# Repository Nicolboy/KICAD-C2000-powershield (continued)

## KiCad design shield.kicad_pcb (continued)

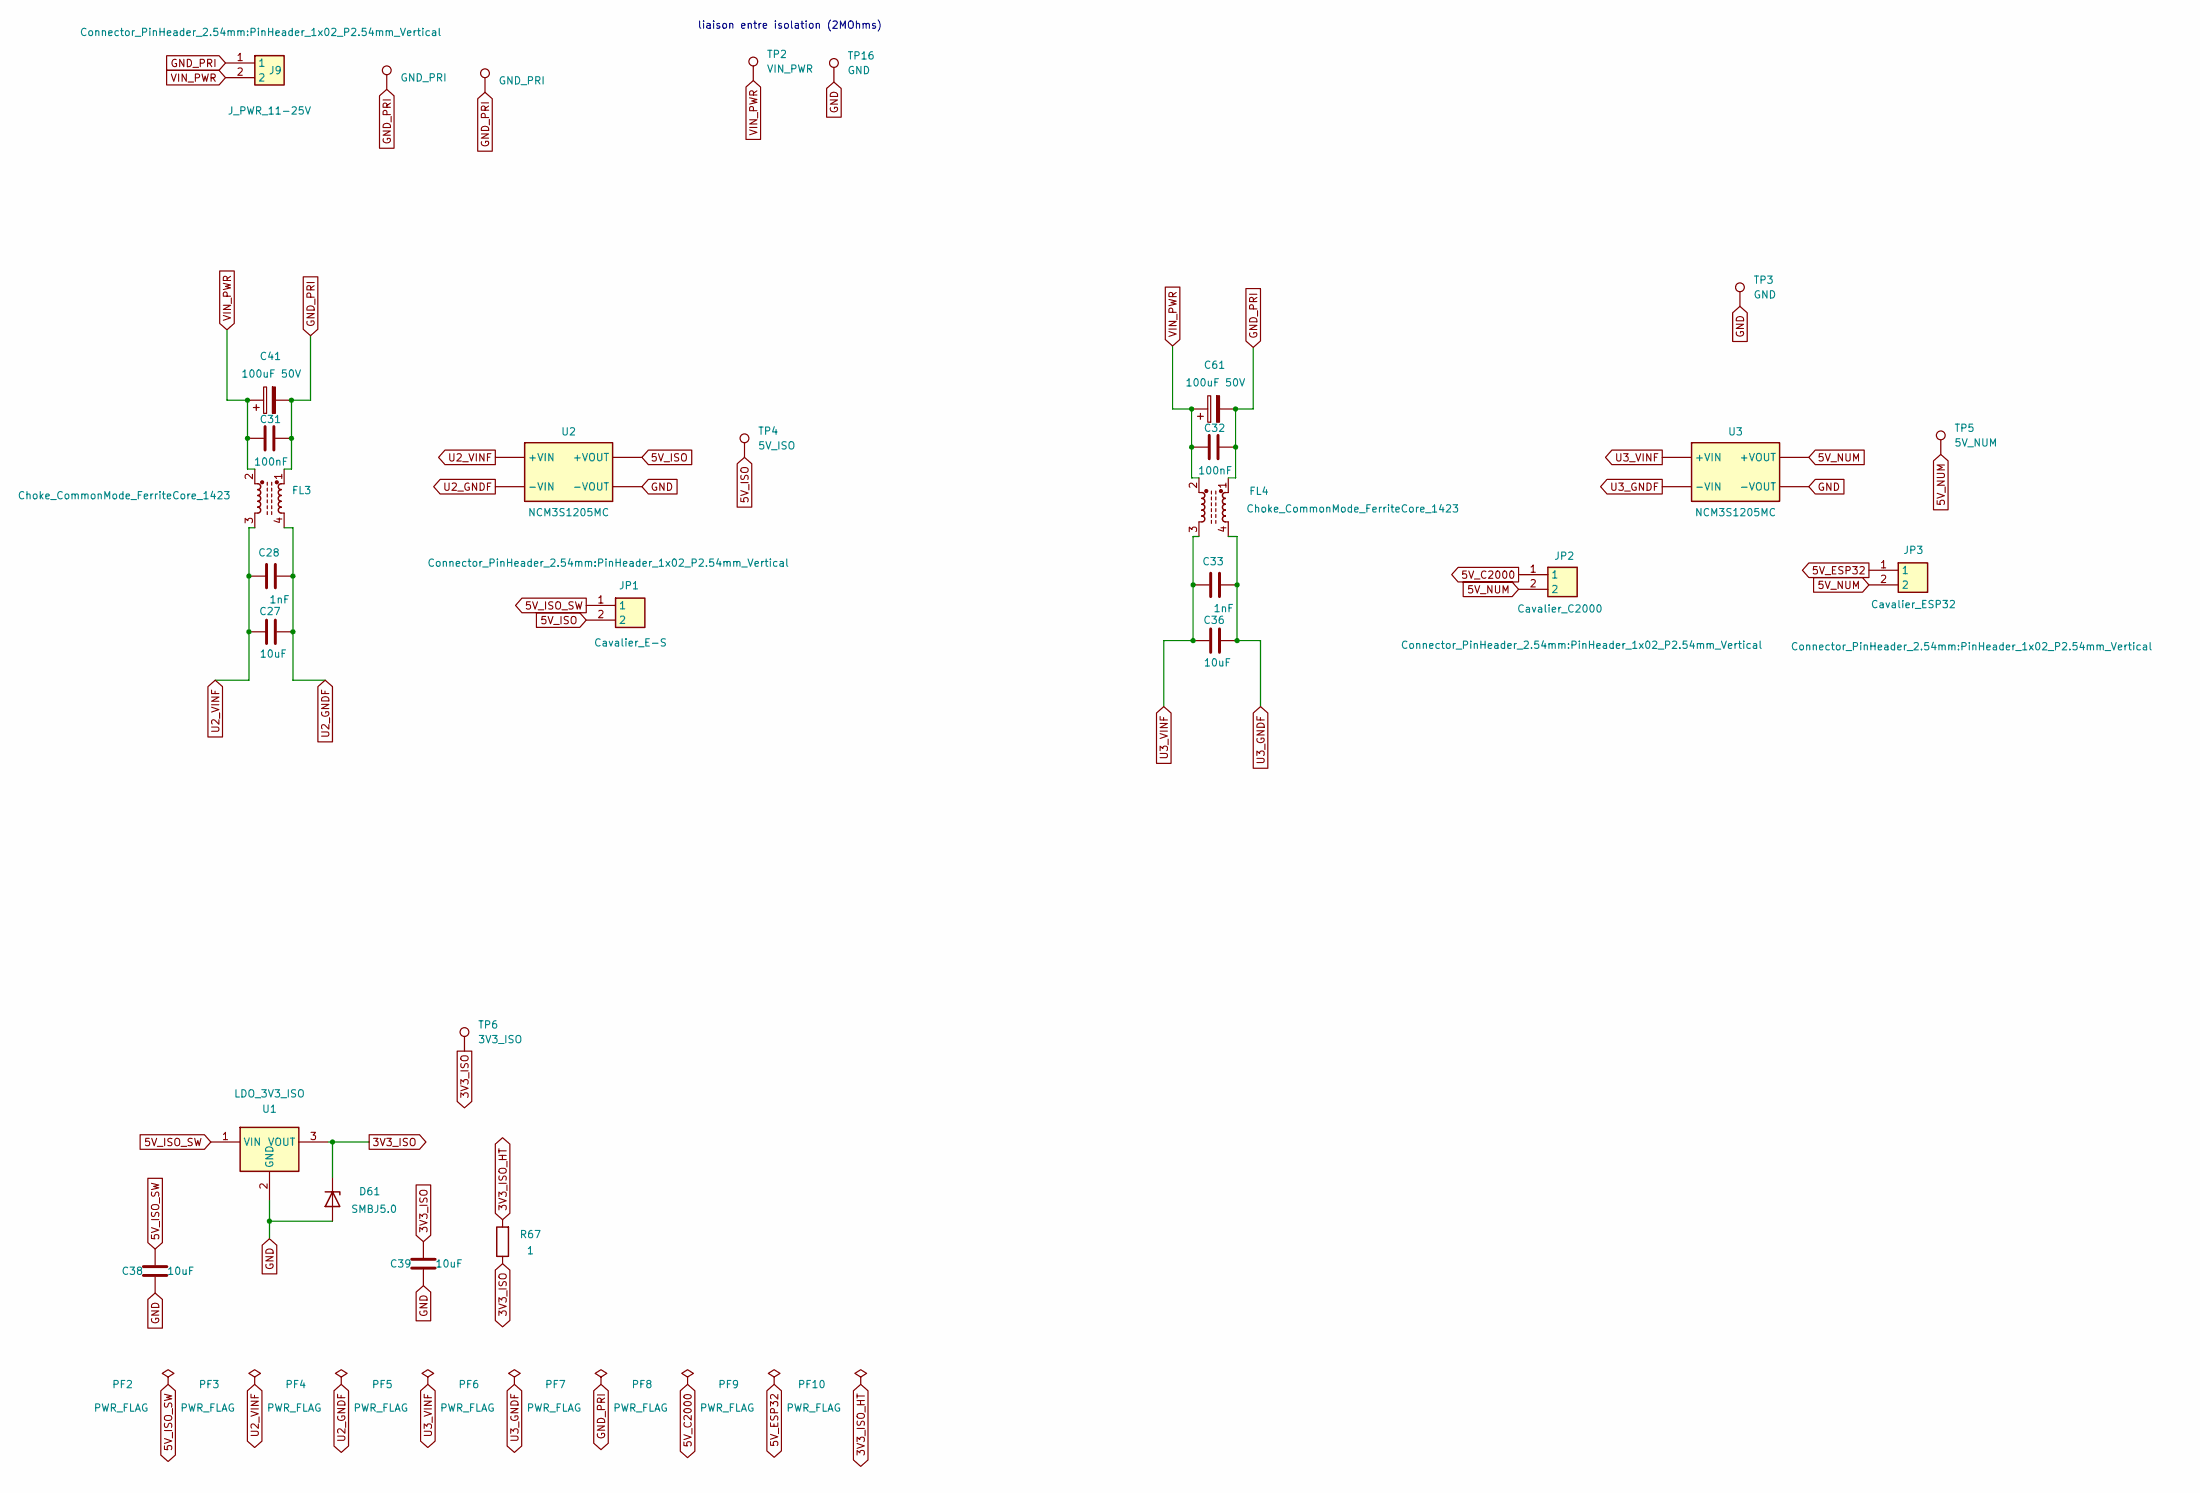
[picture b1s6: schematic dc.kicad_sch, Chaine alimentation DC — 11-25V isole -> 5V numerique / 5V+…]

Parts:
C27, C36, C38, C39: 10uF; C_0805_2012Metric
C28, C33: 1nF; C_0805_2012Metric
C31, C32: 100nF; C_0805_2012Metric
C41, C61: 100uF 50V; CP_Elec_8x10.5
D61: SMBJ5.0; D_SMB
FL3, FL4: Choke_CommonMode_FerriteCore_1423; Filter_Bourns_SRF0905_6.0x9.2mm_My
J9: J_PWR_11-25V; PinHeader_1x02_P2.54mm_Vertical
JP1: Cavalier_E-S; PinHeader_1x02_P2.54mm_Vertical
JP2: Cavalier_C2000; PinHeader_1x02_P2.54mm_Vertical
JP3: Cavalier_ESP32; PinHeader_1x02_P2.54mm_Vertical
PF2, PF3, PF4, PF5, PF6, PF7, PF8, PF9, PF10: PWR_FLAG
R67: 1; R_0805_2012Metric
TP1, TP15: GND_PRI; TestPoint_Pad_D2.5mm
TP2: VIN_PWR; TestPoint_Pad_D2.5mm
TP3, TP16: GND; TestPoint_Pad_D2.5mm
TP4: 5V_ISO; TestPoint_Pad_D2.5mm
TP5: 5V_NUM; TestPoint_Pad_D2.5mm
TP6: 3V3_ISO; TestPoint_Pad_D2.5mm
U1: LDO_3V3_ISO; SOT-23
U2, U3: NCM3S1205MC

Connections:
3V3_ISO: C39.1, D61.1 (K), R67.1, TP6.1 (1_1), U1.3 (VOUT)
3V3_ISO_HT: PF10.1, R67.2; also elsewhere on the board
5V_C2000: JP2.1, PF8.1; also elsewhere on the board
5V_ESP32: JP3.1, PF9.1; also elsewhere on the board
5V_ISO: JP1.2, TP4.1 (1_1), U2.3 (+VOUT)
5V_ISO_SW: C38.1, JP1.1, PF2.1, U1.1 (VIN); also elsewhere on the board
5V_NUM: JP2.2, JP3.2, TP5.1 (1_1), U3.3 (+VOUT)
GND: C38.2, C39.2, D61.2 (A), TP3.1 (1_1), TP16.1 (1_1), U1.2 (GND), U2.4 (-VOUT), U3.4 (-VOUT); also elsewhere on the board
GND_PRI: C31.2, C32.2, C41.2, C61.2, FL3.1, FL4.1, J9.1, PF7.1, TP1.1 (1_1), TP15.1 (1_1); also elsewhere on the board
U2_GNDF: C27.1, C28.2, FL3.4, PF4.1, U2.1 (-VIN)
U2_VINF: C27.2, C28.1, FL3.3, PF3.1, U2.2 (+VIN)
U3_GNDF: C33.2, C36.1, FL4.4, PF6.1, U3.1 (-VIN)
U3_VINF: C33.1, C36.2, FL4.3, PF5.1, U3.2 (+VIN)
VIN_PWR: C31.1, C32.1, C41.1, C61.1, FL3.2, FL4.2, J9.2, TP2.1 (1_1); also elsewhere on the board

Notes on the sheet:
liaison entre isolation (2MOhms)

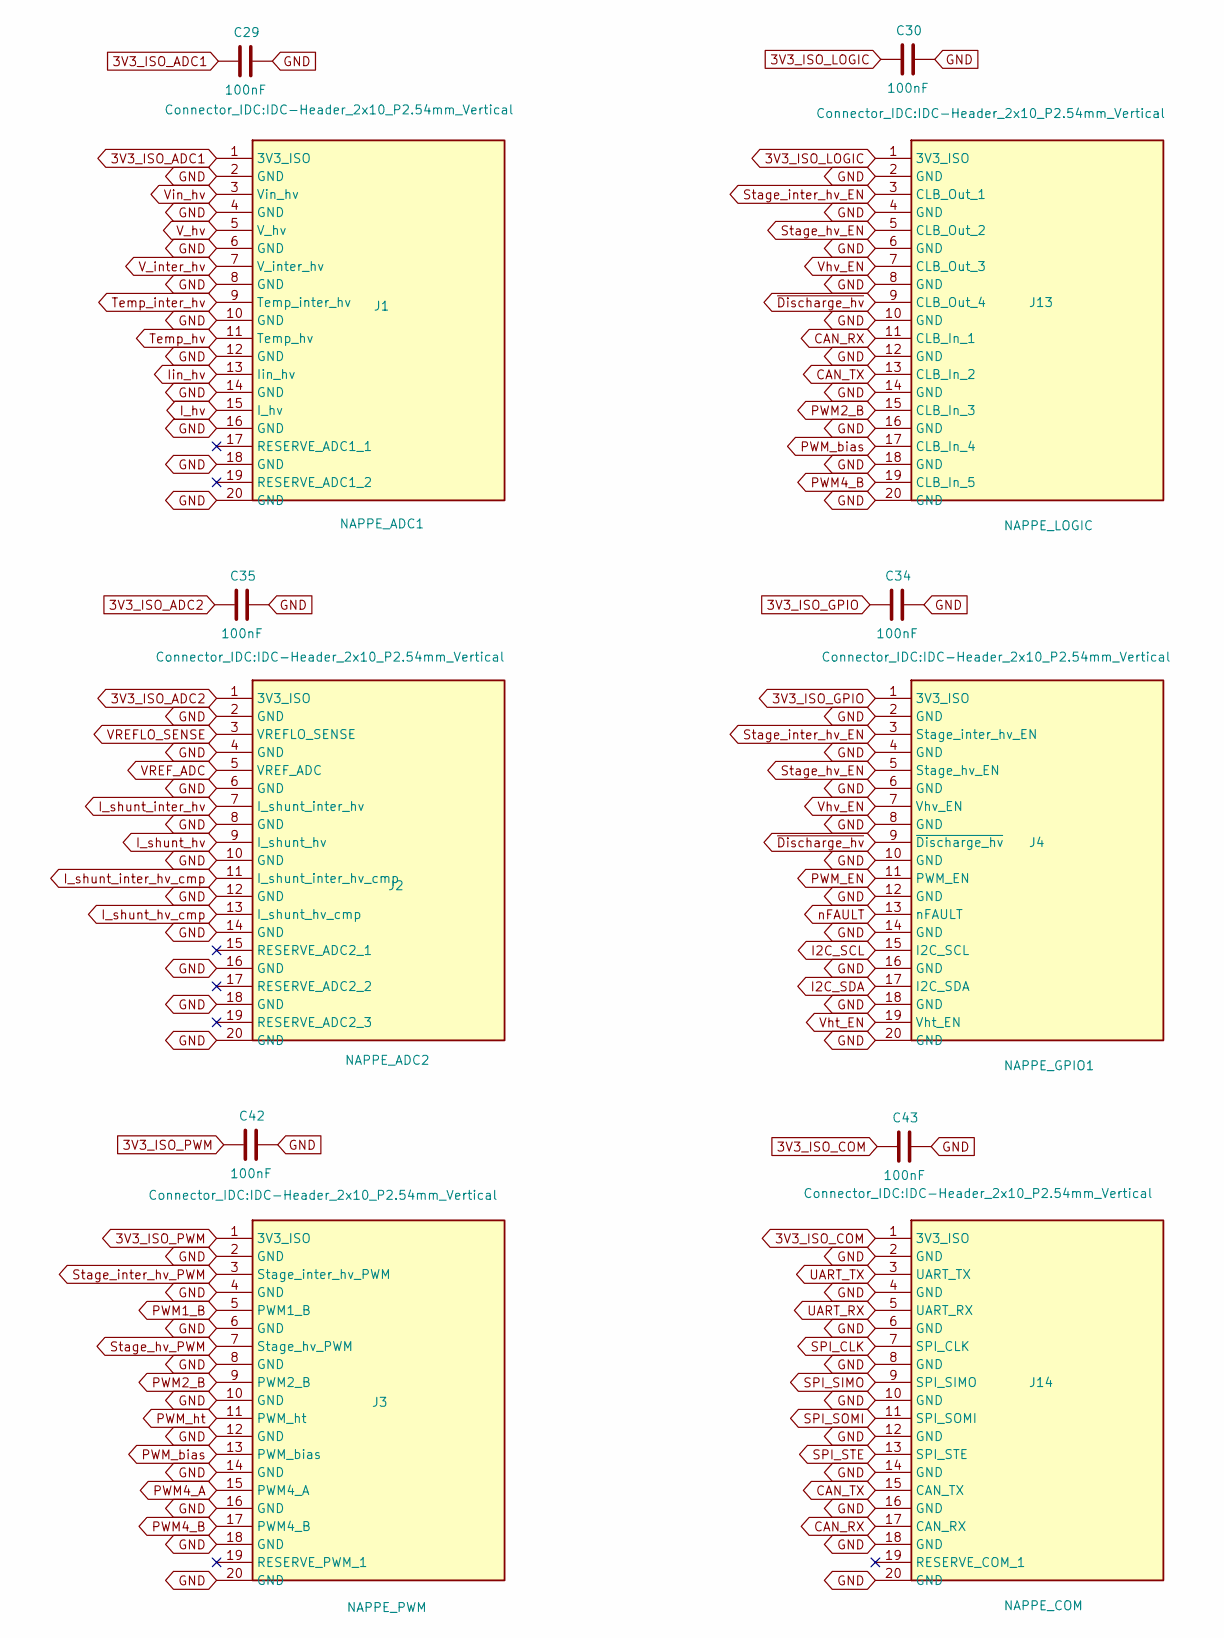
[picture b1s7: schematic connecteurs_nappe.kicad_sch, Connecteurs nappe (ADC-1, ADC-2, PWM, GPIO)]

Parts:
C29, C30, C34, C35, C42, C43: 100nF; C_0805_2012Metric
J1: NAPPE_ADC1; IDC-Header_2x10_P2.54mm_Vertical
J2: NAPPE_ADC2; IDC-Header_2x10_P2.54mm_Vertical
J3: NAPPE_PWM; IDC-Header_2x10_P2.54mm_Vertical
J4: NAPPE_GPIO1; IDC-Header_2x10_P2.54mm_Vertical
J13: NAPPE_LOGIC; IDC-Header_2x10_P2.54mm_Vertical
J14: NAPPE_COM; IDC-Header_2x10_P2.54mm_Vertical

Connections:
3V3_ISO_ADC1: C29.1, J1.1 (3V3_ISO); also elsewhere on the board
3V3_ISO_ADC2: C35.1, J2.1 (3V3_ISO); also elsewhere on the board
3V3_ISO_COM: C43.1, J14.1 (3V3_ISO); also elsewhere on the board
3V3_ISO_GPIO: C34.1, J4.1 (3V3_ISO); also elsewhere on the board
3V3_ISO_LOGIC: C30.1, J13.1 (3V3_ISO); also elsewhere on the board
3V3_ISO_PWM: C42.1, J3.1 (3V3_ISO); also elsewhere on the board
CAN_RX: J13.11 (CLB_In_1), J14.17 (CAN_RX); also elsewhere on the board
CAN_TX: J13.13 (CLB_In_2), J14.15 (CAN_TX); also elsewhere on the board
GND: C29.2, C30.2, C34.2, C35.2, C42.2, C43.2, J1.2 (GND), J1.4 (GND), J1.6 (GND), J1.8 (GND), J1.10 (GND), J1.12 (GND), J1.14 (GND), J1.16 (GND), J1.18 (GND), J1.20 (GND), J2.2 (GND), J2.4 (GND), J2.6 (GND), J2.8 (GND), J2.10 (GND), J2.12 (GND), J2.14 (GND), J2.16 (GND), J2.18 (GND), J2.20 (GND), J3.2 (GND), J3.4 (GND), J3.6 (GND), J3.8 (GND), J3.10 (GND), J3.12 (GND), J3.14 (GND), J3.16 (GND), J3.18 (GND), J3.20 (GND), J4.2 (GND), J4.4 (GND), J4.6 (GND), J4.8 (GND), J4.10 (GND), J4.12 (GND), J4.14 (GND), J4.16 (GND), J4.18 (GND), J4.20 (GND), J13.2 (GND), J13.4 (GND), J13.6 (GND), J13.8 (GND), J13.10 (GND), J13.12 (GND), J13.14 (GND), J13.16 (GND), J13.18 (GND), J13.20 (GND), J14.2 (GND), J14.4 (GND), J14.6 (GND), J14.8 (GND), J14.10 (GND), J14.12 (GND), J14.14 (GND), J14.16 (GND), J14.18 (GND), J14.20 (GND); also elsewhere on the board
I2C_SCL: J4.15 (I2C_SCL); also elsewhere on the board
I2C_SDA: J4.17 (I2C_SDA); also elsewhere on the board
I_hv: J1.15 (I_hv); also elsewhere on the board
I_shunt_hv: J2.9 (I_shunt_hv); also elsewhere on the board
I_shunt_hv_cmp: J2.13 (I_shunt_hv_cmp); also elsewhere on the board
I_shunt_inter_hv: J2.7 (I_shunt_inter_hv); also elsewhere on the board
I_shunt_inter_hv_cmp: J2.11 (I_shunt_inter_hv_cmp); also elsewhere on the board
Iin_hv: J1.13 (Iin_hv); also elsewhere on the board
PWM1_B: J3.5 (PWM1_B); also elsewhere on the board
PWM2_B: J3.9 (PWM2_B), J13.15 (CLB_In_3); also elsewhere on the board
PWM4_A: J3.15 (PWM4_A); also elsewhere on the board
PWM4_B: J3.17 (PWM4_B), J13.19 (CLB_In_5); also elsewhere on the board
PWM_EN: J4.11 (PWM_EN); also elsewhere on the board
PWM_bias: J3.13 (PWM_bias), J13.17 (CLB_In_4); also elsewhere on the board
PWM_ht: J3.11 (PWM_ht); also elsewhere on the board
SPI_CLK: J14.7 (SPI_CLK); also elsewhere on the board
SPI_SIMO: J14.9 (SPI_SIMO); also elsewhere on the board
SPI_SOMI: J14.11 (SPI_SOMI); also elsewhere on the board
SPI_STE: J14.13 (SPI_STE); also elsewhere on the board
Stage_hv_EN: J4.5 (Stage_hv_EN), J13.5 (CLB_Out_2); also elsewhere on the board
Stage_hv_PWM: J3.7 (Stage_hv_PWM); also elsewhere on the board
Stage_inter_hv_EN: J4.3 (Stage_inter_hv_EN), J13.3 (CLB_Out_1); also elsewhere on the board
Stage_inter_hv_PWM: J3.3 (Stage_inter_hv_PWM); also elsewhere on the board
Temp_hv: J1.11 (Temp_hv); also elsewhere on the board
Temp_inter_hv: J1.9 (Temp_inter_hv); also elsewhere on the board
UART_RX: J14.5 (UART_RX); also elsewhere on the board
UART_TX: J14.3 (UART_TX); also elsewhere on the board
VREFLO_SENSE: J2.3 (VREFLO_SENSE); also elsewhere on the board
VREF_ADC: J2.5 (VREF_ADC); also elsewhere on the board
V_hv: J1.5 (V_hv); also elsewhere on the board
V_inter_hv: J1.7 (V_inter_hv); also elsewhere on the board
Vht_EN: J4.19 (Vht_EN); also elsewhere on the board
Vhv_EN: J4.7 (Vhv_EN), J13.7 (CLB_Out_3); also elsewhere on the board
Vin_hv: J1.3 (Vin_hv); also elsewhere on the board
nFAULT: J4.13 (nFAULT); also elsewhere on the board
~Discharge_hv: J4.9 (~Discharge_hv), J13.9 (CLB_Out_4); also elsewhere on the board

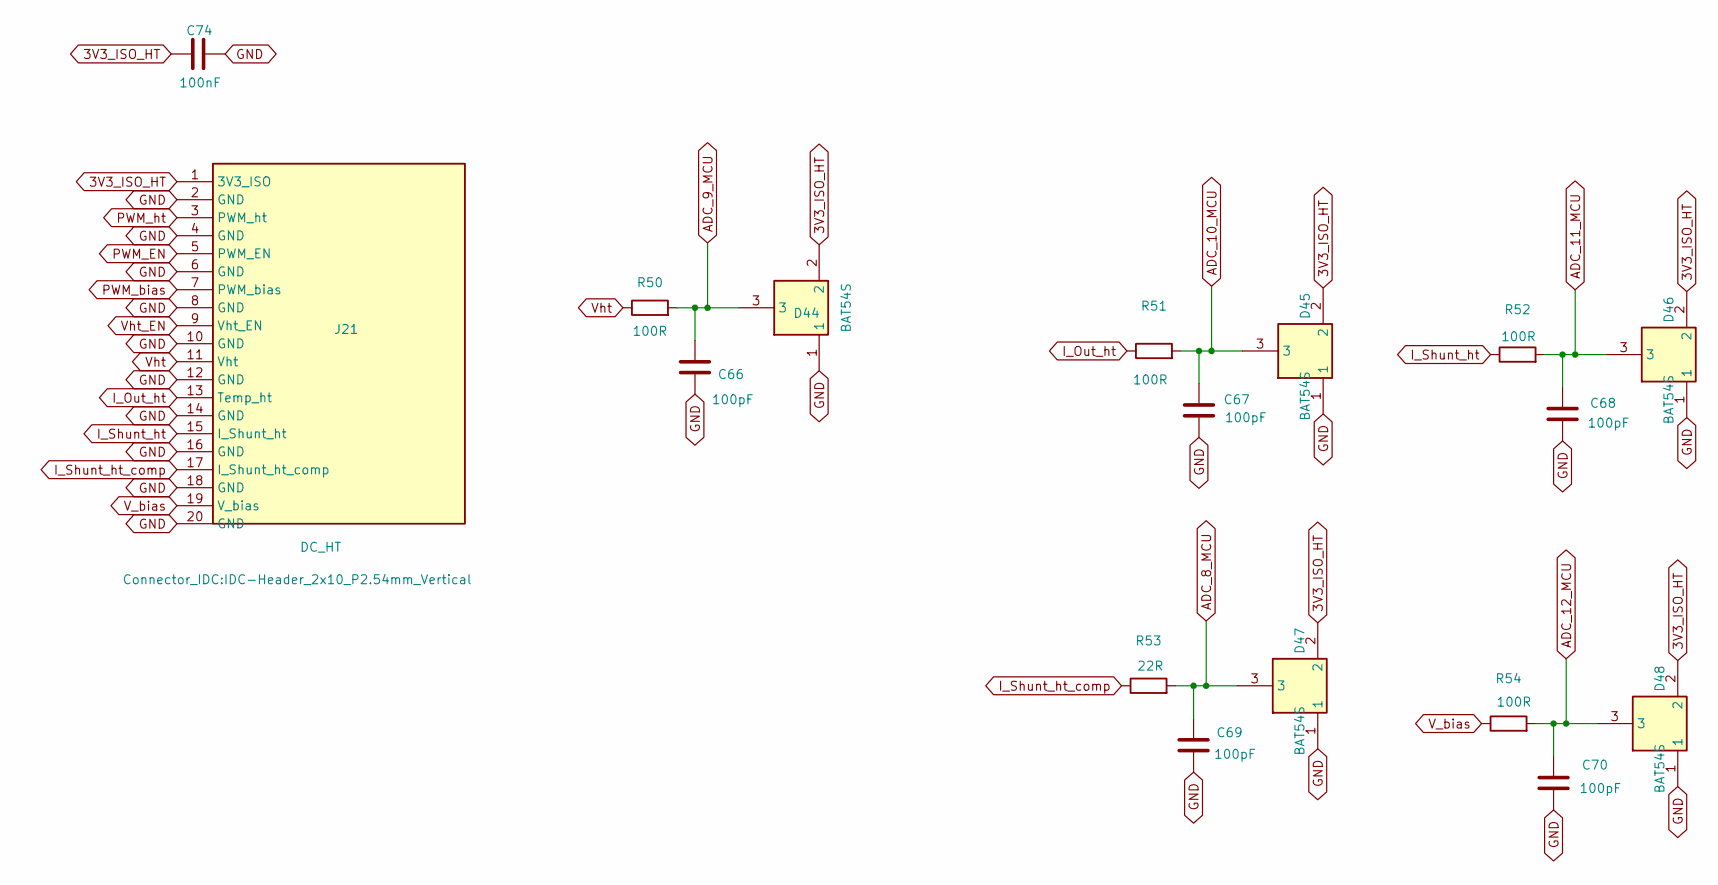
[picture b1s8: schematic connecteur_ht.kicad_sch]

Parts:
C66, C67, C68, C69, C70: 100pF; C_0805_2012Metric
C74: 100nF; C_0805_2012Metric
D44, D45, D46, D47, D48: BAT54S; SOT-23
J21: DC_HT; IDC-Header_2x10_P2.54mm_Vertical
R50, R51, R52, R54: 100R; R_0805_2012Metric
R53: 22R; R_0805_2012Metric

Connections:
3V3_ISO_HT: C74.1, D44.2, D45.2, D46.2, D47.2, D48.2, J21.1 (3V3_ISO); also elsewhere on the board
ADC_8_MCU: C69.1, D47.3, R53.2; also elsewhere on the board
ADC_9_MCU: C66.1, D44.3, R50.2; also elsewhere on the board
ADC_10_MCU: C67.1, D45.3, R51.2; also elsewhere on the board
ADC_11_MCU: C68.1, D46.3, R52.2; also elsewhere on the board
ADC_12_MCU: C70.1, D48.3, R54.2; also elsewhere on the board
GND: C66.2, C67.2, C68.2, C69.2, C70.2, C74.2, D44.1, D45.1, D46.1, D47.1, D48.1, J21.2 (GND), J21.4 (GND), J21.6 (GND), J21.8 (GND), J21.10 (GND), J21.12 (GND), J21.14 (GND), J21.16 (GND), J21.18 (GND), J21.20 (GND); also elsewhere on the board
I_Out_ht: J21.13 (Temp_ht), R51.1
I_Shunt_ht: J21.15 (I_Shunt_ht), R52.1
I_Shunt_ht_comp: J21.17 (I_Shunt_ht_comp), R53.1
PWM_EN: J21.5 (PWM_EN); also elsewhere on the board
PWM_bias: J21.7 (PWM_bias); also elsewhere on the board
PWM_ht: J21.3 (PWM_ht); also elsewhere on the board
V_bias: J21.19 (V_bias), R54.1
Vht: J21.11 (Vht), R50.1
Vht_EN: J21.9 (Vht_EN); also elsewhere on the board

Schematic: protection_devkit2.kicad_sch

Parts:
C11, C12, C13, C14, C15, C16, C17, C18, C19, C20: 100pF; C_0805_2012Metric
D12, D13, D14, D15, D16, D17, D18, D19, D20, D21: BAT54S; SOT-23
R11, R12, R13, R14, R15, R16, R17, R18, R19, R20: 100R; R_0805_2012Metric

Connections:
3V3_ISO_ADC2: D14.2; also elsewhere on the board
3V3_ISO_GPIO: D20.2; also elsewhere on the board
3V3_ISO_PWM: D12.2, D13.2, D15.2, D16.2, D17.2, D18.2, D19.2, D21.2; also elsewhere on the board
CMP_OUT_MCU: C19.2, D20.3, R19.2; also elsewhere on the board
GND: C11.1, C12.1, C13.1, C14.1, C15.1, C16.1, C17.1, C18.1, C19.1, C20.1, D12.1, D13.1, D14.1, D15.1, D16.1, D17.1, D18.1, D19.1, D20.1, D21.1; also elsewhere on the board
PWM1_A_MCU: C12.2, D13.3, R12.2; also elsewhere on the board
PWM1_B: R11.1; also elsewhere on the board
PWM1_B_MCU: C11.2, D12.3, R11.2; also elsewhere on the board
PWM2_A_MCU: C16.2, D17.3, R16.2; also elsewhere on the board
PWM2_B: R15.1; also elsewhere on the board
PWM2_B_MCU: C15.2, D15.3, R15.2; also elsewhere on the board
PWM3_A_MCU: C14.2, D16.3, R14.2; also elsewhere on the board
PWM3_B_MCU: C18.2, D19.3, R18.2; also elsewhere on the board
PWM4_A: R17.1; also elsewhere on the board
PWM4_A_MCU: C17.2, D18.3, R17.2; also elsewhere on the board
PWM4_B: R20.1; also elsewhere on the board
PWM4_B_MCU: C20.2, D21.3, R20.2; also elsewhere on the board
PWM_EN: R19.1; also elsewhere on the board
PWM_bias: R18.1; also elsewhere on the board
PWM_ht: R14.1; also elsewhere on the board
Stage_hv_PWM: R16.1; also elsewhere on the board
Stage_inter_hv_PWM: R12.1; also elsewhere on the board
VREFLO_SENSE: R13.1; also elsewhere on the board
VREFLO_SENSE_MCU: C13.2, D14.3, R13.2; also elsewhere on the board

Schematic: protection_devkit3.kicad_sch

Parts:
C21, C22, C23: 100pF; C_0805_2012Metric
D22, D23, D24: BAT54S; SOT-23
R21, R22, R23: 100R; R_0805_2012Metric
R68, R69: 4.7k; R_0805_2012Metric
TP7: I2C_SDA_MCU; TestPoint_Pad_D2.5mm
TP8: I2C_SCL_MCU; TestPoint_Pad_D2.5mm

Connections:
3V3_C2000: R68.1, R69.1; also elsewhere on the board
3V3_ISO_GPIO: D22.2, D23.2, D24.2; also elsewhere on the board
GND: C21.1, C22.1, C23.1, D22.1, D23.1, D24.1; also elsewhere on the board
I2C_SCL: R21.1; also elsewhere on the board
I2C_SCL_MCU: C21.2, D22.3, R21.2, R68.2, TP8.1 (1_1); also elsewhere on the board
I2C_SDA: R23.1; also elsewhere on the board
I2C_SDA_MCU: C23.2, D24.3, R23.2, R69.2, TP7.1 (1_1); also elsewhere on the board
nFAULT: R22.1; also elsewhere on the board
~FAULT_MCU: C22.2, D23.3, R22.2; also elsewhere on the board

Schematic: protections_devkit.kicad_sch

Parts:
C1, C2, C3, C4, C5, C6, C7, C8, C9: 100pF; C_0805_2012Metric
D2, D3, D4, D5, D6, D7, D8, D9, D10: BAT54S; SOT-23
R1, R2, R3, R4, R5, R6, R7, R8, R9: 100R; R_0805_2012Metric

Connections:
3V3_ISO_ADC1: D2.2, D3.2, D4.2, D5.2, D6.2, D7.2, D9.2; also elsewhere on the board
3V3_ISO_ADC2: D8.2, D10.2; also elsewhere on the board
GND: C1.1, C2.1, C3.1, C4.1, C5.1, C6.1, C7.1, C8.1, C9.1, D2.1, D3.1, D4.1, D5.1, D6.1, D7.1, D8.1, D9.1, D10.1; also elsewhere on the board
I_hv: R7.1; also elsewhere on the board
I_shunt1_MCU: C8.2, D8.3, R8.2; also elsewhere on the board
I_shunt2_MCU: C9.2, D10.3, R9.2; also elsewhere on the board
I_shunt_hv: R9.1; also elsewhere on the board
I_shunt_inter_hv: R8.1; also elsewhere on the board
Iin_MCU: C6.2, D7.3, R5.2; also elsewhere on the board
Iin_hv: R5.1; also elsewhere on the board
Iout_MCU: C7.2, D9.3, R7.2; also elsewhere on the board
Temp1_MCU: C4.2, D6.3, R4.2; also elsewhere on the board
Temp2_MCU: C5.2, D5.3, R6.2; also elsewhere on the board
Temp_hv: R6.1; also elsewhere on the board
Temp_inter_hv: R4.1; also elsewhere on the board
V1_MCU: C1.2, D3.3, R1.2; also elsewhere on the board
V_hv: R2.1; also elsewhere on the board
V_inter_hv: R1.1; also elsewhere on the board
Vin_MCU: C3.2, D4.3, R3.2; also elsewhere on the board
Vin_hv: R3.1; also elsewhere on the board
Vout_MCU: C2.2, D2.3, R2.2; also elsewhere on the board

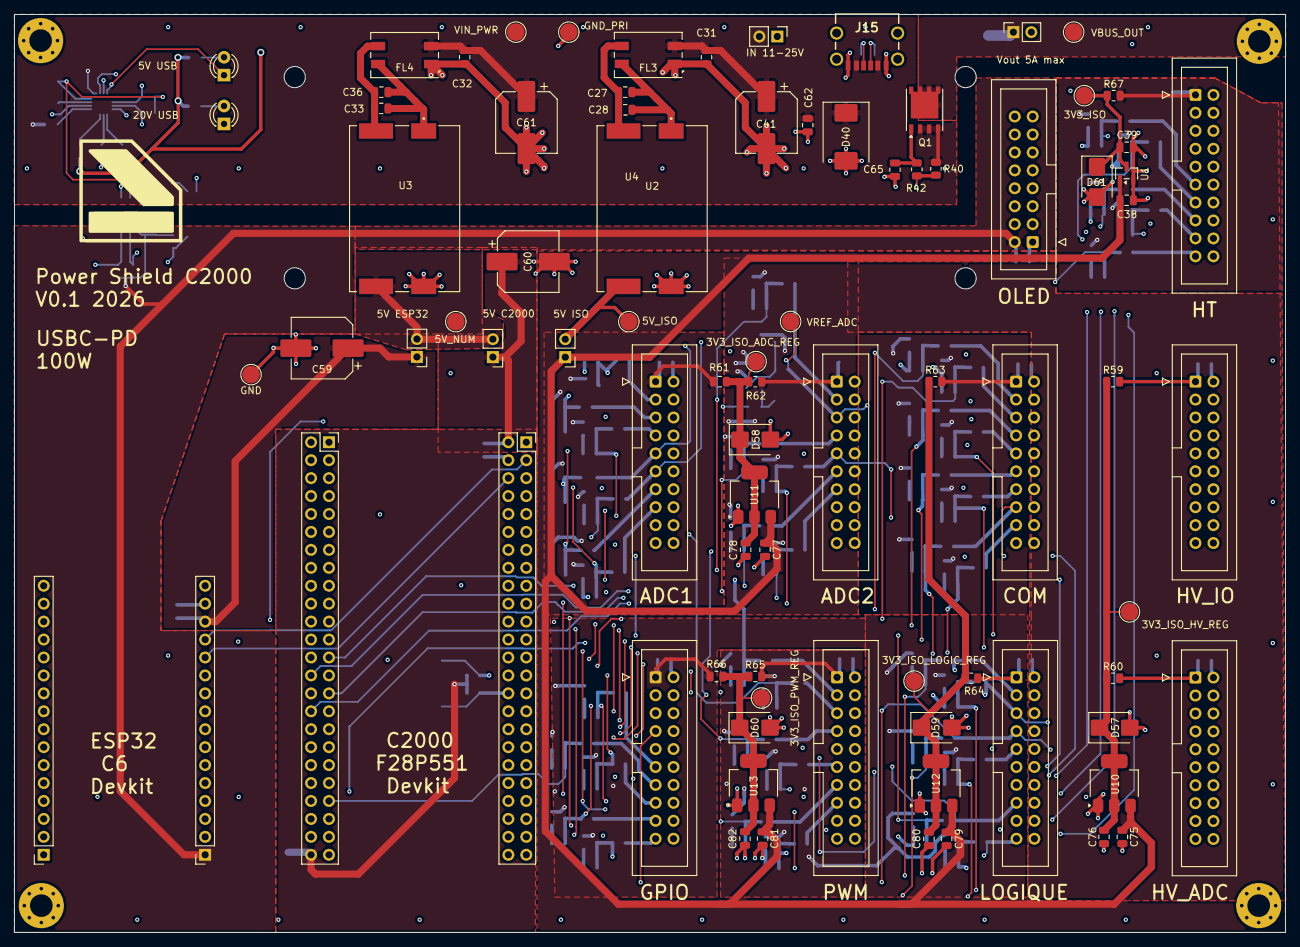
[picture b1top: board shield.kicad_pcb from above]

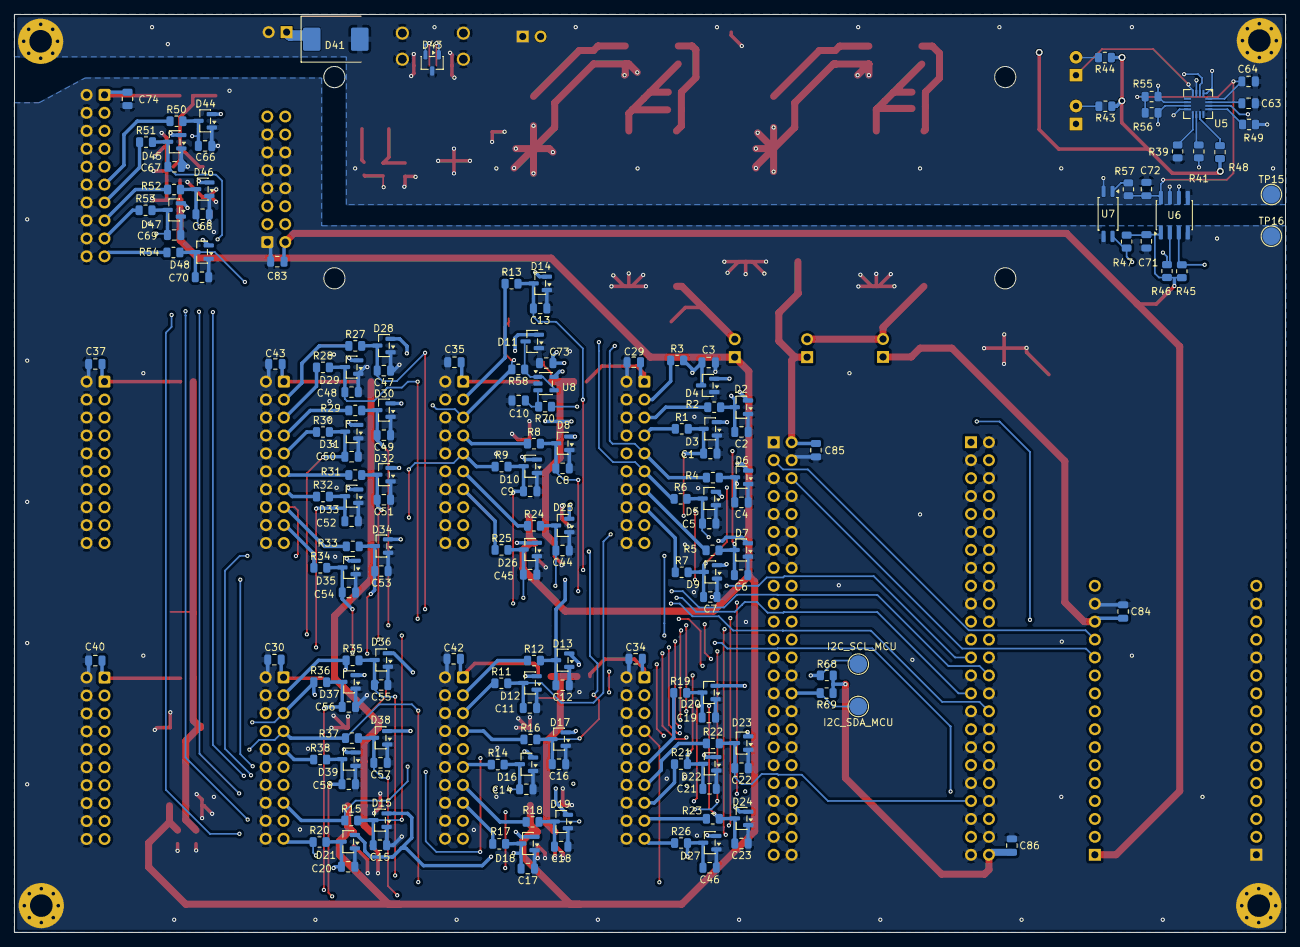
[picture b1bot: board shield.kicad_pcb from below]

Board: 4 copper layers, 180.0 x 130.0 mm, 262 parts (172 on the bottom side), 145 nets.

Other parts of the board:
MECH1: ESP32_C6_Devkit_3D (visuel, sans connexion); ESP32_C6_Devkit_3D
MECH2: DEVKIT_B_F28P551_3D (visuel, sans connexion); DEVKIT_B_F28P551_3D
